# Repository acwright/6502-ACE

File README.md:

6502-ACE
========

An **AC6502** retro-style 8-bit computer based on the **65C02** microprocessor.

> 📖 **Guide:** [AC6502 Documentation](https://acwright.github.io/6502-DOCS/) — the user's and programmer's guide for the whole family.
> Start with [Your ACE](https://acwright.github.io/6502-DOCS/your-ace), the tour of this board.

---

**Building one? Every part you need, with supplier numbers and known issues, is in [BOM.md](BOM.md).**

## Table of Contents

- [Overview](#overview)
- [Architecture](#architecture)
- [Systems](#systems)
- [Software](#software)
- [Hardware](#hardware)
  - [ACE Board](#ace-board)
    - [Known limits](#known-limits)
  - [ACE CF Adapter](#ace-cf-adapter)
  - [ACE RAM Patch](#ace-ram-patch)
- [Which revision to make](#which-revision-to-make)
- [Firmware](#firmware)
  - [Video card](#video-card)
  - [AB Controller](#ab-controller)
- [CAD](#cad)
- [Production](#production)
- [Schematics](#schematics)
- [Shared lines](#shared-lines)
- [Extra pins: `EXP0`–`EXP3` and `HRDB`](#extra-pins-exp0exp3-and-hrdb)
- [Jumpers](#jumpers)
- [Off-board headers](#off-board-headers)
- [Docs](#docs)
- [Checking the schematics](#checking-the-schematics)
- [Checking the banked RAM](#checking-the-banked-ram)
- [Libraries](#libraries)
- [Bill of Materials](#bill-of-materials)
- [License](#license)

---

## Overview

The AC6502 ecosystem is a family of open-source, 65C02-based computers sharing a common architecture, memory map, and [BIOS](https://github.com/acwright/6502-BIOS). Each computer in the family is purpose-built for a different use case but runs the same software and firmware.

The **ACE** (All-in-one Computer Experience) is a complete, self-contained 65C02 computer on a single PCB. It integrates everything found across the COB's modular cards — CPU, memory, video, audio, storage, serial, GPIO, RTC, and keyboard controller — onto one board, delivering the full experience without a backplane or expansion cards.

## Architecture

All AC6502 computers share:

- **CPU**: 65C02 (or accurate emulation)
- **Memory**: 32KB RAM + 32KB ROM, with optional banked RAM expansion
- **Memory Map**: Standardized across the ecosystem — zero page, stack, I/O space ($8000–$9FFF), system ROM, and interrupt vectors at $FFFA–$FFFF
- **Bus**: 16-bit address bus, 8-bit bidirectional data bus, standard 65C02 control signals (RW, PHI2, RESET, IRQ, NMI, RDY, SYNC)
- **BIOS**: A common [BIOS](https://github.com/acwright/6502-BIOS) provides the kernel, monitor, and BASIC interpreter across all systems

## Systems

| Project | Description |
|---------|-------------|
| [6502-ACE](https://github.com/acwright/6502-ACE) | All-in-one Computer Experience — A single board computer (YOU ARE HERE) |
| [6502-COB](https://github.com/acwright/6502-COB) | Computer On a Backplane — Modular desktop computer with expandable card slots |
| [6502-DEV](https://github.com/acwright/6502-DEV) | Development Environment Vehicle — Emulation-based dev system |
| [6502-KIM](https://github.com/acwright/6502-KIM) | Keypad Input Monitor - KIM-1 inspired minimal computer |
| [6502-VCS](https://github.com/acwright/6502-VCS) | Video Computer System — Cartridge-based retro gaming console |

## Software

| Project | Description |
|---------|-------------|
| [6502-BIOS](https://github.com/acwright/6502-BIOS) | The shared BIOS (kernel, monitor, BASIC) for all AC6502 computers |
| [6502-PICOVDP](https://github.com/acwright/6502-PICOVDP) | Firmware for the ACE's video card, on a PICO9918 PRO v2.0 |
| [6502-EMULATOR](https://github.com/acwright/6502-EMULATOR) | Emulator for the whole family — desktop app, browser build, and a command line for scripted runs |
| [6502-PRG](https://github.com/acwright/6502-PRG) | Template project for writing assembly language programs |
| [6502-CRT](https://github.com/acwright/6502-CRT) | Template project for writing assembly language cartridges |
| [6502-ASM](https://github.com/acwright/6502-ASM) | Assembly language example programs and demos |
| [6502-BAS](https://github.com/acwright/6502-BAS) | BASIC program listings |
| [6502-WOZMON](https://github.com/acwright/6502-WOZMON) | Wozmon as a standalone ROM |
| [6502-NOP](https://github.com/acwright/6502-NOP) | An all-NOP ROM, for probing a board during bring-up |
| [6502-DOCS](https://github.com/acwright/6502-DOCS) | The documentation site — the guide, the printable reference cards, branding and label artwork |
| [cffs](https://github.com/acwright/cffs) | Builds CompactFlash disk images for the BIOS filesystem |
| [bastok](https://github.com/acwright/bastok) | Tokenizes BASIC listings into `.prg` images, and back |
| [bin2woz](https://github.com/acwright/bin2woz) | Converts a binary into a Wozmon serial upload |

## Hardware

This repository contains KiCad 7.0+ PCB designs for the ACE board.

### ACE Board
`Hardware/ACE Board/`

The single integrated board hosting the W65C02S CPU and all peripherals. Provides:

- **CPU**: W65C02S running at 1 MHz
- **RAM**: 32KB SRAM (62256) + Optional 512K banked SRAM (AS6C4008)
- **ROM**: 32KB EEPROM (28C256)
- **Video**: PICO9918 PRO v2.0 running [6502-PICOVDP](https://github.com/acwright/6502-PICOVDP) (VGA 640×480); see [Video card](#video-card). The silkscreen and the BOM's value field say `Pico9918A`
- **Audio**: ARMSID SID chip emulator (3-voice synthesis, RCA output)
- **Storage**: Storage adapter socket
- **Serial**: R6551AP ACIA with MAX238 level shifter (RS-232 via DB9, 50–19200 baud). Male DB-9 wired
  as **DTE**, like a PC, so reaching a laptop needs a **null-modem** cable. `RTS`, `DTR` and `DSR`
  always reach the cable; the `CTS EN` and `DCD EN` jumpers (J2 and J4) pick ground or the cable for
  those two inputs — **both default to ground**
- **GPIO**: 65C22 VIA (20 GPIO pins, 2× 16-bit timers, shift register)
- **RTC**: DS1511Y real-time clock with battery-backed NVRAM
- **Keyboard Controller**: ATmega1284 running AB Controller firmware
- **Input**: PS/2 keyboard connector and 8×8 keyboard matrix header
- **Joystick**: Two Atari 2600-compatible joystick ports (JOYSTICK A on VIA PORT A and JOYSTICK B on VIA PORT B, `J6` and `J8`), read as `JOY(2)` and `JOY(1)` respectively
- **Clock**: 16 MHz DIP-14 full can oscillator (X1); drives the ATmega1284 at 16 MHz and, through the 74HC163 divider (U5), the 65C02, VIA, ACIA and SID at 1 MHz, the speed every AC6502 is tested at. The PHI2 SELECT jumper (J1) offers 2 MHz on pins 2 and 3.
  - **Rev 1.0: keep J1 on 1 MHz** (pins 1 and 2). Its SID is clocked from the 1 MHz output whatever J1 says, so at 2 MHz it answers only every other CPU cycle.
  - **Rev 1.1: 2 MHz is an option at the builder's risk.** The CPU, VIA, ACIA and SID all follow J1. The limit found at 2 MHz, tested on 2026-11-11, is the RAM letting go of the data bus too soon after `PHI2` falls: a fast RAM (the Alliance AS6C62256 at U7) with a fast-releasing 74HC00 lot at U14, the gate that makes `RB` and `WB`, misread at 2 MHz. Rev 1.1 fits a 74HCT00 at U14, which ends `RB` and `WB` a few nanoseconds later; it ran an hour's read-and-write soak at 2 MHz clean. A slower RAM (a Hitachi HM62256LP-70) also cures it. The cure was found by testing, not measured with a scope. The R6551AP is rated for 2 MHz, with no margin, and read back clean at that speed. BIOS 2.1.0 finds the CompactFlash card at boot at 2 MHz, and reads and writes it clean there (tested on Rev 1.0 with the 74HCT00 at U14, 2026-11-12); BIOS 2.0.x misses the card at boot at 2 MHz.

**The serial handshake jumpers.** `CTS EN` and `DCD EN` (J2 and J4) both default to **ground**, and
that is how the boards were built. Ground means the line is permanently asserted, so the ACIA can
always send and always receive. Moved to the cable, they do real work — measured on a real R6551 in
2026: `CTS` high stops the transmitter dead and `DCD` high stops the receiver, losing the byte that
arrives. A board jumpered to the cable and plugged into something that does not assert those lines
shows no banner and no echo at all, and looks broken when it is not.
- **Reset**: Manual reset button (SW70, just above <kbd>Esc</kbd>) connected to the ATmega1284, which also provides power-on reset to the 65C02
- **Power**: 5V DC via barrel jack, center-positive. Rev 1.1 has reverse-polarity protection (`D5`); Rev 1.0 has none

**Cards on `CART` and `BUS`.** `IRQB`, `NMIB` and `RESB` are shared by several devices on the board and by
anything plugged into `CART` and `BUS` (J17 and J18). A card may only pull
those lines low, open-drain, and must never drive them high: a device that drives a shared line high holds it
there against every other device that pulls it low. A video card built around a pico9918 has the same `/INT`
problem as U3, and needs the same diode on the card.

#### Known limits

- **The SID probe:** BIOS 2.0.x missed the SID (an ARMSID) at 1 MHz about once in a dozen boots, because it read voice 3 only once. BIOS 2.1.0 reads it several times: on 2026-11-12 it found the ARMSID on 10 boots of 10, and with IO7 switched off on IO ENABLE (SW69) found no SID on 10 of 10. Use 2.1.0 or later.
- **The CompactFlash probe:** BIOS 2.0.x waited for the card with a loop counted in CPU cycles, about 851 ms at 1 MHz and half that at 2 MHz, so a slow card could be missed. BIOS 2.1.0 passes over an empty slot at once and otherwise waits up to 3.0 s at 1 MHz (1.5 s at 2 MHz). A Promaster 128 MB card is ready in about 434 ms.

### ACE CF Adapter
`Hardware/ACE CF Adapter/`

A CompactFlash adapter board that connects to the Storage header on the ACE Board. Provides:

- **Interface**: 8-bit IDE (True IDE) mode
- **Storage**: CompactFlash socket. The BIOS filesystem divides the card into 256 disk banks of 1 MB each, so 256 MB is the usable capacity regardless of the card fitted
- **Revisions**: Rev 1.0 is the board on sale, and its silkscreen says `J21` for STORAGE and `J3` for the CF socket. See the [revision history](REVISIONS.md#ace-cf-adapter)

### ACE RAM Patch
`Hardware/ACE RAM Patch/`

A patch board for Rev 1.0 of the ACE Board that corrects the extended RAM (banked SRAM) decoding, with the same logic as Rev 1.1. U12 and U13 come off the ACE, chips and sockets, and the patch is soldered underneath in their place. Provides:

- **Fix**: `LOADL` and `LOADH` go high only on a write to the bank register, `$83FF` or `$87FF`, while PHI2 is high. Rev 1.0 pulsed both latches whenever the bus was idle, and the first patch (Rev 1.0) fixed that but still loaded a latch on any write to `$8300`–`$83FE` and `$80FF`–`$82FF` (and the same in the `$8400` window)
- **Interface**: two DIP-14 footprints of pin headers, J1 into U12's holes and J2 into U13's, soldered on both boards. The patch mounts front side up under the ACE, so its layout is not mirrored; U13's pin 1 is 23.00 mm from U12's pin 1 along the row
- **Layout**: U1, J1, J2 and U2 in one row, 92.6 × 13.1 mm. J1 and J2 are on the front, facing the ACE; U1 (74HC00) and U2 (74HC02) are on the back, hanging below, so trim their leads flush on the front. The patch hangs about 8.5 mm below the ACE: the header, the board, and the chips
- **Rev 1.1**: replaces the Rev 1.0 patch, which plugged into U13 alone
- **Status**: Rev 1.1 is verified on hardware. Its decode passes `Tests/check-schematics.mjs`, and on 2026-11-03 an ACE Board Rev 1.0 with the patch fitted passed `node Tests/check-ram.mjs --expect FF` with every card in place: `HW_PRESENT` read `$FF` after each of 10 restarts, each latch loaded only on its own address, and every bank of both windows held its own patterns, with 0 failures in 3 runs. The same board had 0 failures in 3 runs without the video card and the CF Adapter, reading `$77`. Without the patch, a Rev 1.0 reads `$FD`, because the BIOS doesn't find the `$8400` window. See [Checking the banked RAM](#checking-the-banked-ram)

<!-- Which revision to make: generated by Tools/revision-audit/register.py from Tools/data/orders.json. Edit that file, not this section. -->
## Which revision to make

**Make the newest revision of a board, and check its label first.** The table below gives each board's newest revision. A newer revision fixes what was found on the older ones. Every revision, old and new, is in [REVISIONS.md](REVISIONS.md), with what changed in each.

Each revision carries one of three labels:

- **Tested:** This revision was built and tested.
- **Proven design:** Not built at this revision, but its circuit is a tested revision's. The only changes are silkscreen text, part values, mounting holes, outline clean-up, parts moved a fraction of a millimetre onto their grid, capacitor pitch, socket outlines, a footprint swap with the same holes, a solder jumper's default, the solder mask or paste at a card edge, or tracks rerouted or pours refilled with DRC and the netlist check passing. A builder can treat it as tested.
- **Untested:** The circuit, the power path or the layout changed in a way that only a built board proves, or the board has never been built at all.

[BOM.md](BOM.md) has the parts for every revision, and its known issues.

| Board | Newest revision | Label | Why |
|---|---|---|---|
| ACE Board | 1.1 | **Untested** | A new bank-latch decode (its logic is proven on the ACE RAM Patch 1.1), a 74HCT00 at U14, the PHI2 SELECT jumper with the SID on the CPU's clock, the ACIA's crystal jumpers, and a 1N5819 in the power path. On the first build, measure `VCC` at full load: it must stay above 4.5 V. |
| ACE CF Adapter | 1.1 | **Proven design** | Annotation only. The new LCSC socket fits the same footprint, but no board has been built with it yet. |
| ACE RAM Patch | 1.1 | **Tested** | Built and tested on an ACE Board Rev 1.0, 2026-11-03. |
<!-- End of which revision to make -->

## Firmware

This repository contains [PlatformIO](https://platformio.org/)-based firmware for the ACE board. The video card's firmware is [6502-PICOVDP](https://github.com/acwright/6502-PICOVDP), and the ROM is [6502-BIOS](https://github.com/acwright/6502-BIOS).

### Video card

The ACE runs a PICO9918 PRO v2.0 (RP2354A) with 6502-PICOVDP, and BIOS 2.x. RP2040 PICO9918 boards (v1.x) can't run 6502-PICOVDP.

1. **Fit the `MDE1` pin:** solder one 0.1″ header pin into the PRO's `MDE1` pad.
2. **Optionally, back up the stock firmware** from BOOTSEL: `picotool save -a stock.bin`. To restore it later, `picotool load -v -x stock.bin`. The backup has been made on a PRO; the restore is picotool's ordinary load and hasn't been tried.
3. **Flash 6502-PICOVDP:** download `picovdp-v1.0.0.uf2` from the [v1.0.0 release](https://github.com/acwright/6502-PICOVDP/releases/tag/v1.0.0) (SHA-256 `0b74cd9875cbffc46de7ec48a9bb6e0d4a76a3e796d2563615e17e6bed94afd5`). Hold BOOT, connect USB-C, and run `picotool load -v -x -f picovdp-v1.0.0.uf2`. The release build has no USB of its own, so every update needs BOOT again. The card can be flashed in the ACE's socket with the ACE switched off.
4. **Burn BIOS 2.x to U8.** The ACE was tested with `v2.0.2`.
5. **Check the first boot:** the AC6502 logo, then `AC6502 BIOS v2.1`, `BASIC v2.0 30718 BYTES FREE` and `RAM RTC CF SER VIA SID VDP`, at power-on and after the reset button (SW70). If `VDP` is missing from that line, the card isn't running 6502-PICOVDP.
6. **Check the `MDE1` pin** from BASIC: `POKE 39939,4:POKE 39939,142:PRINT PEEK(39939):POKE 39939,0:POKE 39939,142` prints 172.

On Rev 1.0, fit the `/INT` diode first (see [Building a Rev 1.0](BOM.md#build-notes)).

### AB Controller
`Firmware/AB Controller/`

Firmware for the ATmega1284 keyboard controller on the ACE board. Provides:

- Dual keyboard input: PS/2 and 8×8 matrix keyboard simultaneously
- PS/2 scancode to ASCII conversion
- Matrix keyboard scanning with hardware debouncing
- Modifier key support: Shift (symbols/punctuation) and Ctrl (control codes)
- Buffered output via 65C22 VIA with CA1/CB1 data-ready strobes
- Independent enable/disable for PS/2 and matrix inputs, releasing PORT A / PORT B so the 6502 can read the joysticks that share them
- 6502 reset control: pulls `RESB` low on PC7, open-drain, holding the CPU in reset for ~250 ms at power-on, and debounces the reset button on PC0
- Optional jiffy clock: pulses `NMIB` low from the DS1511Y SQW input, open-drain; compiled out unless `ENABLE_SQW` is defined. The `ENABLE_SQW` build compiles, but hasn't been run on hardware

See [Firmware/AB Controller/README.md](./Firmware/AB%20Controller/README.md) for setup and usage instructions.

## CAD
`CAD/`

3D-printable enclosure bases and laser-cut top panels for the ACE system.

**Board images** are in `CAD/Images/<Board>/Rev X/`: `Front.png` and `Back.png` on white, and `Front Transparent.png` and `Back Transparent.png` with no background. Every image is a 3D render at the same size, with the black solder mask and white silkscreen the boards are made with. Bare-board photos may differ, because the renders show parts fitted.

**Top panels and jigs are versioned by board revision**, like `Hardware/`: `CAD/Tops/<Board>/Rev X/`, `CAD/Jigs/<Board>/Rev X/`. Each revision has its own complete folder, even when two revisions share the same files. `Bases/` holds the parts for a whole computer, not for one board, so it isn't versioned.

The **[plate mounting drawing](CAD/Bases/Plate%20Mounting%20Drawing.png)** ([SVG](CAD/Bases/Plate%20Mounting%20Drawing.svg)) shows where the ACE Board and the ACE CF Adapter mount on the base plate, with every hole's position and the hardware the build needs. The plate is a stack of three 3 mm acrylic layers.

## Production
`Production/`

[REVISIONS.md](REVISIONS.md) lists every board revision: whether it was made, its JLCPCB order, the commit it was made from, and what fits it.

JLCPCB-ready Gerber files and BOM/CPL for PCB fabrication and assembly.

## Schematics
`Schematics/`

PDF schematics for the ACE board.

## Shared lines

Five lines of the 6502 bus are shared by every board on it: `RESB`, `IRQB`, `NMIB`, `RDY` and `BE`. A board may pull one of these lines low, and nothing drives one high. Each line is held high by one 10kΩ pull-up resistor to VCC, on the board with the CPU: the ACE Board, the KIM Board, the VCS Main Board, the COB CPU Card or CPU Card Pro, or the DEV Board. No other board has one. Two pull-ups on the same line would sit in parallel and lower its resistance, so a card that adds its own pull-up changes the machine for every other board. The VIAs and PIAs in the BOMs, the W65C22N and W65C21N, have open-drain interrupt outputs for this reason.

**Interrupt outputs.** Whatever drives `IRQB` or `NMIB` may only pull it low. Every board is drawn for the parts in its BOM and works as shipped, with no jumper to cut or bridge:

- **A part whose interrupt output is open-drain** (the W65C22N, W65C21N, R6551AP, DS1511Y and TMS9918A) drives the line directly, or through a diode with a solder jumper across it that ships bridged. The diode is fitted either way. To use a part that drives its interrupt high as well as low instead, such as a W65C22S or a replacement of your own, cut the jumper: the diode then lets the part only pull the line low. A board with no diode in the line can't take such a part.
- **A part that drives its interrupt high as well as low** (the pico9918, the VERA module, and a microcontroller such as the ATmega1284 or a Raspberry Pi Pico) reaches the line through a diode, a BAT85 or a 1N914, with its cathode toward the part. Where a solder jumper sits across that diode, it ships open. The diode is then the only path to the line, so fit it, and never bridge the jumper, because the part would then hold the line high against every other interrupt source.
- **A microcontroller wired to the line directly,** as on the ACE Board, the Mega Helper and the Flash Helper, drives it open-drain in its firmware: it sets the pin low or leaves it as an input, and never drives it high.

The *Jumpers* section below gives each board's interrupt jumper.

The same holds where a board has its own reset circuit. A reset switch, its timer and the transistor that pulls `RESB` low can be on any board, such as the COB Backplane Pro or the Clock Card, but the `RESB` pull-up is only ever on the board with the CPU. Each of those boards draws its pull-ups together, in one group on its schematic.

The DEV Board is the exception on `RESB`. It stands in for a Main Board, so it owns reset: its Reset button goes to the Teensy, and the Teensy drives `RESB` onto the bus through U3, a level shifter that only sends signals out, as it drives `PHI2`. U3 holds `RESB` high or low, so the DEV Board has no `RESB` pull-up, and nothing else on its bus may pull `RESB` low. Connect a DEV only to a passive backplane, never to the COB Backplane Pro, whose reset circuit would pull against U3, and don't fit a card that pulls `RESB` low, such as the COB RTC Card.

`SOB` is a CPU pin that isn't on the bus. It is tied to VCC, directly or through a 10kΩ resistor.

A few chips have a pull-up of their own inside the chip, such as an ATmega's reset pin. Where such a pin is wired to `RESB`, its pull-up of 30–60kΩ sits in parallel with the 10kΩ one. That's harmless, because whatever pulls `RESB` low can sink the extra current many times over.

A revision that doesn't follow this yet says so in its known issues in [BOM.md](BOM.md), with what to fit or remove.

## Extra pins: `EXP0`–`EXP3` and `HRDB`

`EXP` stands for "extra pin". Four pins of the 6502 bus are left for a builder's own use: pin 4 is `EXP1`, pin 6 is `EXP0`, pin 19 is `EXP3` and pin 21 is `EXP2`.

Pins 4 and 6 have a second job. A cartridge ties both of them to GND. That pulls `HRDB` ("High ROM disable bar", active low) low on the board with the ROM, which takes `$C000–$FFFF` away from the ROM so that the cartridge answers there instead. So in a build that uses cartridges, pins 4 and 6 are reserved for `HRDB`, and nothing else may drive them. They are free as `EXP1` and `EXP0` only in a build that never uses cartridges. `EXP2` and `EXP3` are always free.

How the boards treat pins 4 and 6:

- **The ACE Board and the KIM Board** join them to their ROM's `HRDB` input, and their silk says `HRDB`. The VCS Main Board joins them the same way from Rev 1.1.
- **The COB Memory Card** joins them to its `HRDB` only through jumpers: fit two shunts on J2, or bridge JP1 and JP2, in a COB that takes cartridges. It is the only board with these jumpers, because the COB is the experimenter's build. The VCS Main Board Rev 1.0 had them too (J5, or JP3 and JP4); fit them, because the VCS always takes cartridges.
- **A cartridge** (the ROM Cart, the Flash Cart, the KIM Keypad Card) ties them to GND.
- **A board that only carries the bus through**, such as a backplane or a helper, calls them `EXP1` and `EXP0`, as its silk does, and a note on its schematic says what they carry.

<!-- Jumpers: generated by Tools/jumpers/gen.py from Tools/data/jumpers.json. Edit that file, not this section. -->
## Jumpers

Some boards have solder jumpers, and pin headers that take a shunt. The tables below give every one: what it's for, how the board is shipped, and what to do with it. The **Needed** column marks the ones that matter:

- **To run**: the board doesn't work until this is set. Set it before the first power-up.
- **For serial**, **For interrupts**, **For cartridges**: the board runs without it, but that feature doesn't.
- Blank: leave it as shipped unless you want what it offers.

Where a header needs a shunt, the board's BOM lists it.

**ACE Board**

| Rev | Jumper | What it's for | As shipped | What to do | Needed |
|---|---|---|---|---|---|
| 1.0 | J1 | `PHI2 SELECT`: the CPU clock, 1 MHz (pins 1 and 2) or 2 MHz (pins 2 and 3). | No shunt. | Fit the shunt on pins 1 and 2, 1 MHz: at 2 MHz the sound chip, whose clock is always 1 MHz, answers only every other cycle. With no shunt the CPU has no clock. | To run |
| 1.0, 1.1 | J2 | `CTS`: where the ACIA's `CTS` comes from. | No shunt. | Fit the shunt on pins 1 and 2, ground, as the boards are built. On pins 2 and 3 it takes `CTS` from the cable, and a cable that doesn't assert it stops the transmitter. With no shunt the input floats, and serial may not work. | For serial |
| 1.0, 1.1 | J4 | `DCD`: where the ACIA's `DCD` comes from. | No shunt. | Fit the shunt on pins 1 and 2, ground, as the boards are built. On pins 2 and 3 it takes `DCD` from the cable, and a cable that doesn't assert it stops the receiver. With no shunt the input floats, and serial may not work. | For serial |
| 1.1 | J1 | `PHI2 SELECT`: the CPU clock, 1 MHz (pins 1 and 2) or 2 MHz (pins 2 and 3). | No shunt. | Fit the shunt on pins 1 and 2, 1 MHz, the speed every AC6502 is tested at. Pins 2 and 3 run the CPU, VIA, ACIA and sound chip at 2 MHz together, at the builder's risk: see *Clock*. With no shunt the CPU has no clock. | To run |
| 1.1 | JP1, JP2 | Options for the ACIA's crystal: JP1 puts R38 (1M) across it, and JP2 adds C32 (22pF) to ground. | Both open. | Leave them open for the R6551AP, the part the board is tested with. Close both for a Rockwell R65C51P1 or R65C51P2, whose oscillator won't start on the bare crystal (an R65C51P2 ran clean this way on a Serial Card on 2026-11-11), or for a WDC W65C51. |  |

<!-- End of jumpers -->

<!-- Off-board headers: generated by Tools/offboard/gen.py from Tools/offboard/offboard.json, Tools/data/offboard.json and the PCB files. Edit those, not this section. -->
## Off-board headers

Some boards have small headers, such as `RESET SW`, `CLOCK ENBL SW`, `POWER LED` and `VCC`, that a standard build leaves empty. They are for a machine built into a full enclosure, which AC6502 doesn't offer today. In such a build, the parts a person handles are mounted on the case and wired to the board through these headers: the power jack, the switches, the LEDs and the keyboard. The matching parts on the board are then left off. For example, an ACE Board can sit inside a case with its power jack, power switch and key switches left off, and a Keyboard Helper as its keyboard.

To build a board for a case:

1. Fit the header, and wire the part on the case to it. The table says what goes on each pin.
2. Leave off the parts on the board that the table names. A button on the case can work beside the board's own button, but some parts, such as an LED that shares the board's resistor, can't share.
3. Set any jumper the table mentions. The [Jumpers](#jumpers) section has the rest.

The connector follows the kind of build. A single-board machine, the ACE Board or the KIM Board, uses plain 2.54 mm pin headers, which are simpler and cheaper. A board in a multi-board machine, every COB board and the separate boards of the VCS, the DEV and the KIM, uses JST XH, the family's standard for these headers.

The table lists every off-board header on each board's newest revision, read from the board's PCB file.

| Board | Rev | Header | Label | Connector | What it's for | Leave off |
|---|---|---|---|---|---|---|
| ACE Board | 1.1 | J3 | `RESET SW` | Pin header, 1×2, 2.54 mm | A reset button on the case. The header is wired across SW70, the board's own reset button. | SW70, if the case covers it. Both buttons reset the machine if it stays. |
| ACE Board | 1.1 | J15 | `AUDIO` | Pin header, 1×2, 2.54 mm | Audio to a jack or an amplifier on the case: the same signal as J11 and J14, on pin 1, with ground on pin 2. | J11 and J14, if the case has its own jack. They can stay fitted beside it. |
| ACE Board | 1.1 | J19 | `VCC` | Pin header, 1×2, 2.54 mm | Power from a jack and a switch on the case: 5 V on pin 1, ground on pin 2. The header is on `VCC` itself, past D5, the reverse-polarity diode, and SW68, the power switch. | J16, the barrel jack, and SW68, the power switch. Nothing on the board protects this header, so the case's supply must be a regulated 5 V, wired the right way around. |
| ACE Board | 1.1 | J20 | `POWER LED` | Pin header, 1×2, 2.54 mm | A power LED on the case: anode to pin 1 (`VCC`), cathode to pin 2, which runs through R26 to ground. | D1, the board's own power LED. It shares R26, so with both fitted each gets half the current. |
| ACE Board | 1.1 | J22 | `KEYBOARD` | Pin header, 1×16, 2.00 mm | The keyboard matrix: `PA0`–`PA7` on pins 1–8 and `PB0`–`PB7` on pins 9–16. A keyboard on the case, such as a Keyboard Helper, connects here. | The key switches, SW1–SW67. |

<!-- End of off-board headers -->

## Docs
`Docs/`

**[ACE Board Rev 1.0 Build Notes](Docs/ACE%20Board/Rev%201.0/ACE%20Board%20Build%20Notes.pdf)** (PDF, for printing): the work a Rev 1.0 needs beyond its bill of materials, step by step. That is the pull-up values, the ACIA, the supply capacitor, the `RESB` pull-up and firmware, the `/INT` diode's socket stack and fitting the ACE RAM Patch, followed by the meter checks and the first power-on.

## Checking the schematics
`Tests/check-schematics.mjs`

The banked RAM's latch enables were wrong in Rev 1.0, and wrong again in a different way in the first RAM Patch, and both times the gates looked right on paper. This script checks the logic instead of reading it. It asks KiCad for each board's netlist, builds the glue logic from the gates it finds there, and drives every address, as a read and as a write, with PHI2 high and low and with a cartridge in and out. That is 524,288 bus states per board. For each one it compares every chip select, read and write strobe, and bank latch enable against the memory map, and checks that exactly one chip drives the data bus on a read and exactly one takes a write. A net that nothing drives counts as a failure, so a missing wire fails too.

It checks two boards: Rev 1.1, and Rev 1.0 with the ACE RAM Patch Rev 1.1 fitted. The patch's headers name the sockets they plug into (`74HC00 (U12)`), and the script pulls those chips and joins each header pin to its socket's net. For Rev 1.1 it also checks that the CPU, VIA, ACIA and SID all run from U5's 1 MHz output, that the video card's `/INT` reaches `IRQB` only through a diode, and that `RESB` has a pull-up.

Run it after any change to either schematic:

```sh
node Tests/check-schematics.mjs
```

It needs Node.js and KiCad's `kicad-cli`, which it finds on the `PATH`, at the macOS default location, or through a `KICAD_CLI` environment variable. It takes about 15 seconds, prints `ok` or `FAIL` for each check with example bus states for any failure, and exits non-zero on a failure.

## Checking the banked RAM
`Tests/check-ram.mjs`

`check-schematics.mjs` checks the logic as it is drawn. This script checks a built board, including its chips, its solder joints and, on a Rev 1.0, its ACE RAM Patch. It talks to the machine over the serial port. It restarts the machine ten times and reads `HW_PRESENT` after each boot, then loads `Tests/check-ram.asm` over XMODEM and runs it three times. The program does three things:

- **Marks every bank.** Each of the 256 banks in both windows gets a marker that names the bank.
- **Checks that each latch loads only on its own address.** With a bank selected, it writes a different value to every data address in the window, then reads every address, including the bank register. A latch that loaded by mistake would change the bank, and the markers would show it. It also checks that the other window's latch hasn't moved, and that a write to the bank register does change the bank, so a stuck latch can't pass.
- **Checks every byte.** It writes all 1023 data bytes of every bank in both windows, and only then reads them back, with three patterns. Two of the patterns are complements, so every bit is tested as both 0 and 1. The byte behind each bank register, `$83FF` and `$87FF`, isn't tested.

The boot probe alone can't confirm the decode fix. The BIOS tests only banks 0 and 1, so a machine with the first RAM Patch's decode still finds its RAM.

Connect the ACE's serial port, start it at BASIC's prompt on BIOS 2.x, and run:

```sh
node Tests/check-ram.mjs
```

With every card fitted, add `--expect FF` to require that exact `HW_PRESENT`. Without it, only the two RAM bits have to be set. `--port`, `--runs` and `--restarts` change the defaults; the top of the script lists them.

It needs Node.js, [cc65](https://cc65.github.io/) and `stty`, so it runs on macOS and Linux. It takes about four minutes, works with or without a video card, and exits non-zero on a failure. **It erases the BASIC program in memory and everything in the banked RAM.**

`Tests/check-ram-fault.cjs` shows that the test can fail. It runs the program on the [emulator](https://github.com/acwright/6502-EMULATOR) with a fault added to the emulated RAM card: the first RAM Patch's decode, a stuck latch bit, or a latch that never loads. Each fault has to produce failures. The file's header has the command.

## Libraries
`Libraries/`

Shared KiCad symbol and footprint libraries used across all AC6502 hardware projects, with their 3D models in `Models/`. A part is named for what it is and its shape, such as `RJ45 Jack LED` or `CR2032 Holder`, never for a manufacturer's part number, so a replacement part with the same footprint fits without renaming anything. The part numbers to buy are in [BOM.md](BOM.md). Every AC6502 repository carries the same copy of each part.

## Bill of Materials

Every part for every board, by revision, is in **[BOM.md](BOM.md)**, with supplier numbers, known issues, build notes and files to upload to Digi-Key and Mouser. What changed in each revision, and what is known about each one, is in **[REVISIONS.md](REVISIONS.md)**.

## License

Hardware designs are released under the [CERN Open Hardware Licence Version 2 – Permissive](https://ohwr.org/cern_ohl_p_v2.txt).
Firmware is released under the [MIT License](./Firmware/AB%20Controller/LICENSE).

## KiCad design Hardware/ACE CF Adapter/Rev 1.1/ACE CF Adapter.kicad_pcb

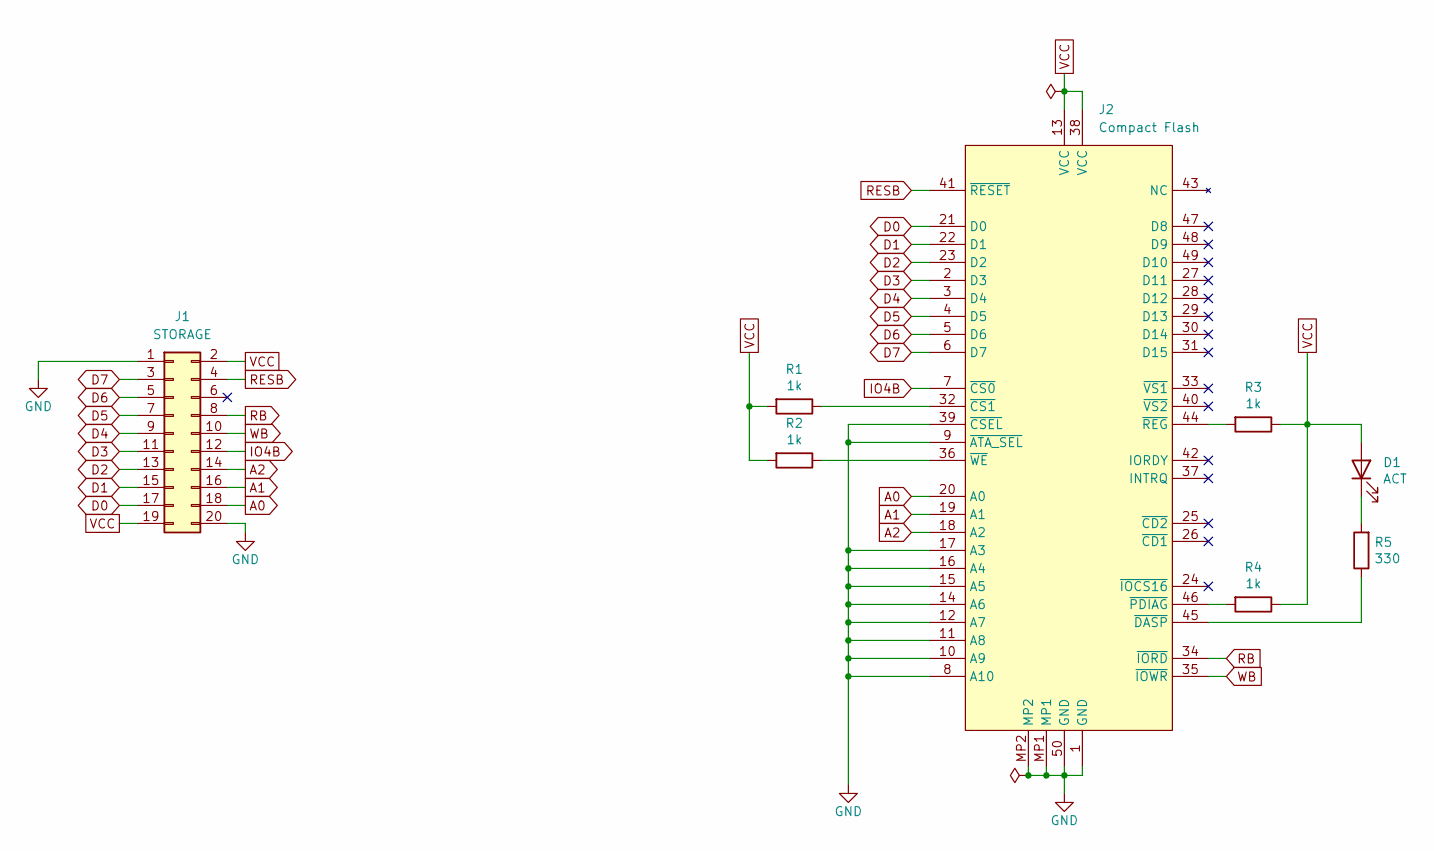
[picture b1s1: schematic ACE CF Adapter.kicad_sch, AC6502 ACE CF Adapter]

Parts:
D1: ACT; LED_D3.0mm; Digikey 732-5008-ND
J1: STORAGE; PinHeader_2x10_P2.54mm_Horizontal; Digikey 609-3338-ND
J2: Compact Flash; CompactFlash Socket; Digikey 4827-101D-TAAB-R01-ND
R1, R2, R3, R4: 1k; R_Axial_DIN0204_L3.6mm_D1.6mm_P5.08mm_Horizontal; Digikey 13-MFR-12FTF52-1KCT-ND
R5: 330; R_Axial_DIN0204_L3.6mm_D1.6mm_P5.08mm_Horizontal; Mouser 603-MFR-12FTF52-330R

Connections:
A0: J1.18, J2.20 (A0)
A1: J1.16, J2.19 (A1)
A2: J1.14, J2.18 (A2)
D0: J1.17, J2.21 (D0)
D1: J1.15, J2.22 (D1)
D2: J1.13, J2.23 (D2)
D3: J1.11, J2.2 (D3)
D4: J1.9, J2.3 (D4)
D5: J1.7, J2.4 (D5)
D6: J1.5, J2.5 (D6)
D7: J1.3, J2.6 (D7)
GND: J1.1, J1.20, J2.1 (GND), J2.8 (A10), J2.9 (~ATA_SEL), J2.10 (A9), J2.11 (A8), J2.12 (A7), J2.14 (A6), J2.15 (A5), J2.16 (A4), J2.17 (A3), J2.39 (~CSEL), J2.50 (GND), J2.MP1, J2.MP2
IO4B: J1.12, J2.7 (~CS0)
unnamed: D1.1 (K), R5.2
unnamed: J2.32 (~CS1), R1.1
unnamed: J2.45 (~DASP), R5.1
unnamed: J2.46 (~PDIAG), R4.2
unnamed: J2.44 (~REG), R3.2
unnamed: J2.36 (~WE), R2.1
RB: J1.8, J2.34 (~IORD)
RESB: J1.4, J2.41 (~RESET)
VCC: D1.2 (A), J1.2, J1.19, J2.13 (VCC), J2.38 (VCC), R1.2, R2.2, R3.1, R4.1
WB: J1.10, J2.35 (~IOWR)

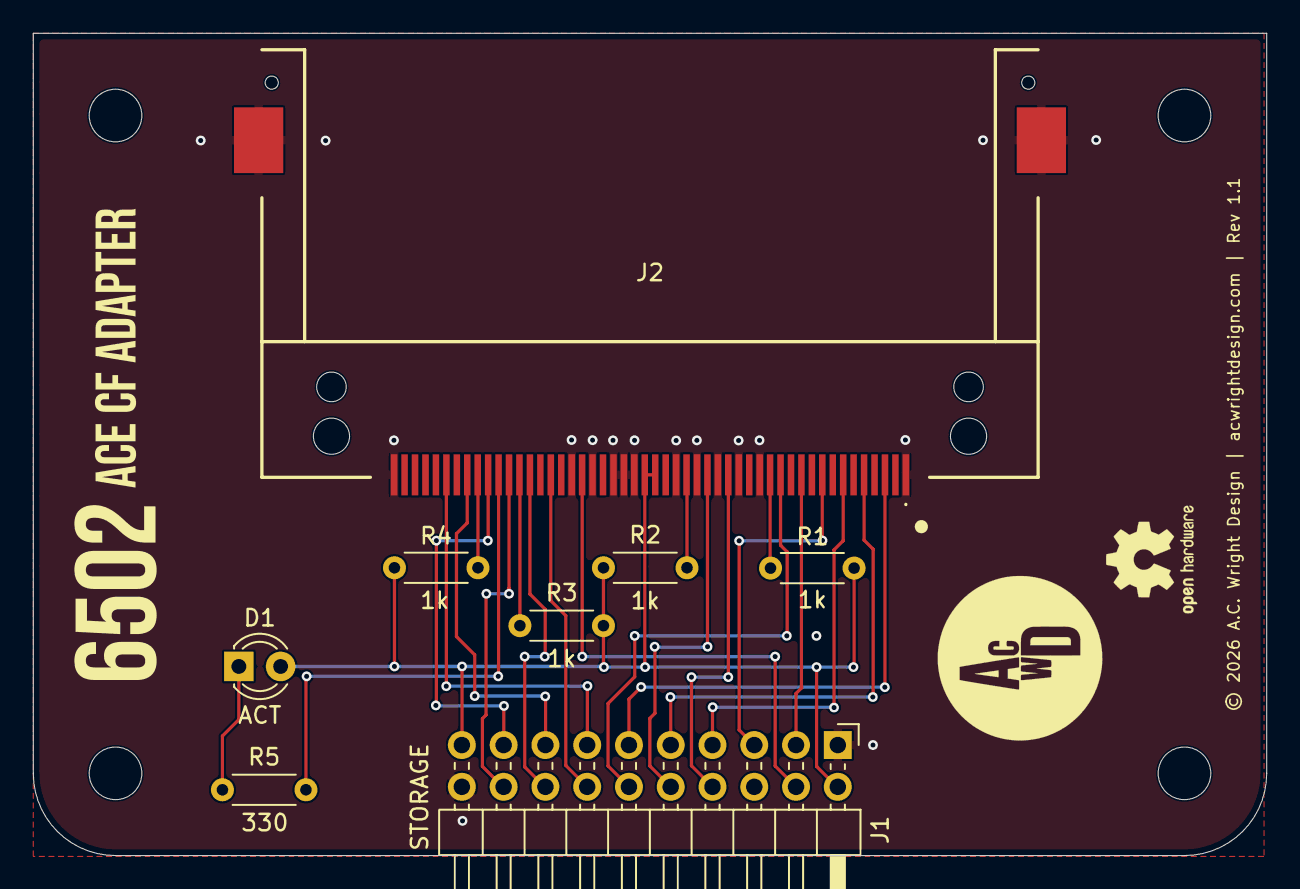
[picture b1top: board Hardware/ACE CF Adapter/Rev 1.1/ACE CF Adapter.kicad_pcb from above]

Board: 2 copper layers, 75.0 x 50.0 mm, 8 parts (0 on the bottom side), 23 nets.

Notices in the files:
Hardware/ACE Board/Rev 1.1/ACE Board.kicad_pcb:
© 2026 A.C. Wright Design | acwrightdesign.com | Rev 1.1
Hardware/ACE CF Adapter/Rev 1.0/ACE CF Adapter.kicad_pcb:
© 2026 A.C. Wright Design | acwrightdesign.com | Rev 1.0
